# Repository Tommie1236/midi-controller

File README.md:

<!---->

### huge thanks to the amazing [rp2040 skeleton project](https://github.com/daveythacher/RP2040_SKELETON). it helped immensly setting up this project. i probably couldn't have done it without

# &lt;still need good name :)&gt;
#### A lighting focused midi controller

---
### Why?
I started this project as i wanted phisical controls to go with the [mydmx3](https://www.adj.com/mydmx-3) dmx controller software.  
Mydmx3 practicly only support midi as data in/out next to dmx out. So a midi controller it is.  
There are more than enough midi controllers on the market but almost all of them are audio focused in the controls. I couldn't really vind any that i would like for controlling lighting. So i decided to design and build my own.

### Requirements
I set a couple of requirements that i definetly wanted in my controler. As following:  
#### Controls:

- **motorized faders**. Mostly for dimming controls, enough in the playback section and 1 as Master.  
  I chose motorized so they could sync with the controlling software if the value changes and for for example if you were to switch banks to a new set of controls. (mydmx doesn't support that but i wanted to design my controller to work with almost anything.)

- **Buttons**. for playbacks/executors en general control, a whole lot.  
  Of Course. what would a controller be without a lot of buttons. I also want them to have black with transparent text keycaps and rgb leds below to show the status of the button.

- **Encoders**. Mostly speed control but could also be dimmer, at least 1 per "channel"/collumn and a couple spare.
  I wanted some encoders to be able to change the speed of scene/cue playbacks. But also for for example a dimmer channel dat isn't changed often but often enough to have phisical controls for.

- **Small Displays/Scribble Strips**. channel/collumn names, one per channel/collumn.  
  To show what cue/scene was mapped to that channel/collumn. If i implement bank switching inside the controller (as mydmx doesn't support like anything. only the most basic midi triggering) i want to see what cue i have mapped on that fader/buttons.
  And maybe also to show the fader/encoder value when changing. For if you want it to a specific value and the visual position isn't enough.

- **Keypad**. just one, numbers 0-9 + some modifiers.  
  Should speak for itself. just general number inputs and modifiers.

- **"Master" Display**. (relatively) big display, just one.  
   A around 3a4" touch display for configuration of the controller and general info. Main controls for anything happening inside the controller.

- **Leds**. A lot. most RGB some just Amber.  
  I want all the buttons to have a seperate controllable RGB led to show the buttons status. and about 16 mono Amber leds around the encoders to show their value.

#### Conectivity:

- **usb midi**. one usb-B port.
  To connect to a pc running for example mydmx.

- **hardware midi**. 2 or 3 din-5 ports.
  To connect to other midi gear or any controller that has hardware midi ports on it. Should have the same data as the usb midi port

- **External Switch Ports**. 2a3 x 1/4" jack.
  To connect external footswitches or pedals. should support normal on/off footswitches and maybe one or 2 can have analog value support.

- **Desk Light**. xlr-4?.
  A xlr connector that support a lot of desk lights. preferably xlr-4 so it isn't confused with audio or dmx signals. Sadly there isn't a standard for desk ligths as far as i can find.

- **Powercon Socket**. Blue one. maybe also power out.  
  Of cource. It needs some power to run. prefereably powercon (true1??) but a C14 socket would also work.  
  with the motor faders and a lot of leds. Usb supplied power wont be enough.

#### And here are some features i want to support but arent required for the mvp: 

- **USB Hub**. Probably USB-A sockets.  
  To connect more devices downstream from the controller

- **RTP MIDI**. Wifi/Ethernet  
  Using a ESP32 or similar to handle the network stack and enable the controller to communicate either wireless or via a ethernet cable.  
  Adding to the already available midi connection options of USB-MIDI and hardware-MIDI

- **Web Server**.  
  Maybe a configuration webserver as the display will be quite small. would also run on the ESP32 that handels the network.  
  it connects to the main rp2040 using uart.

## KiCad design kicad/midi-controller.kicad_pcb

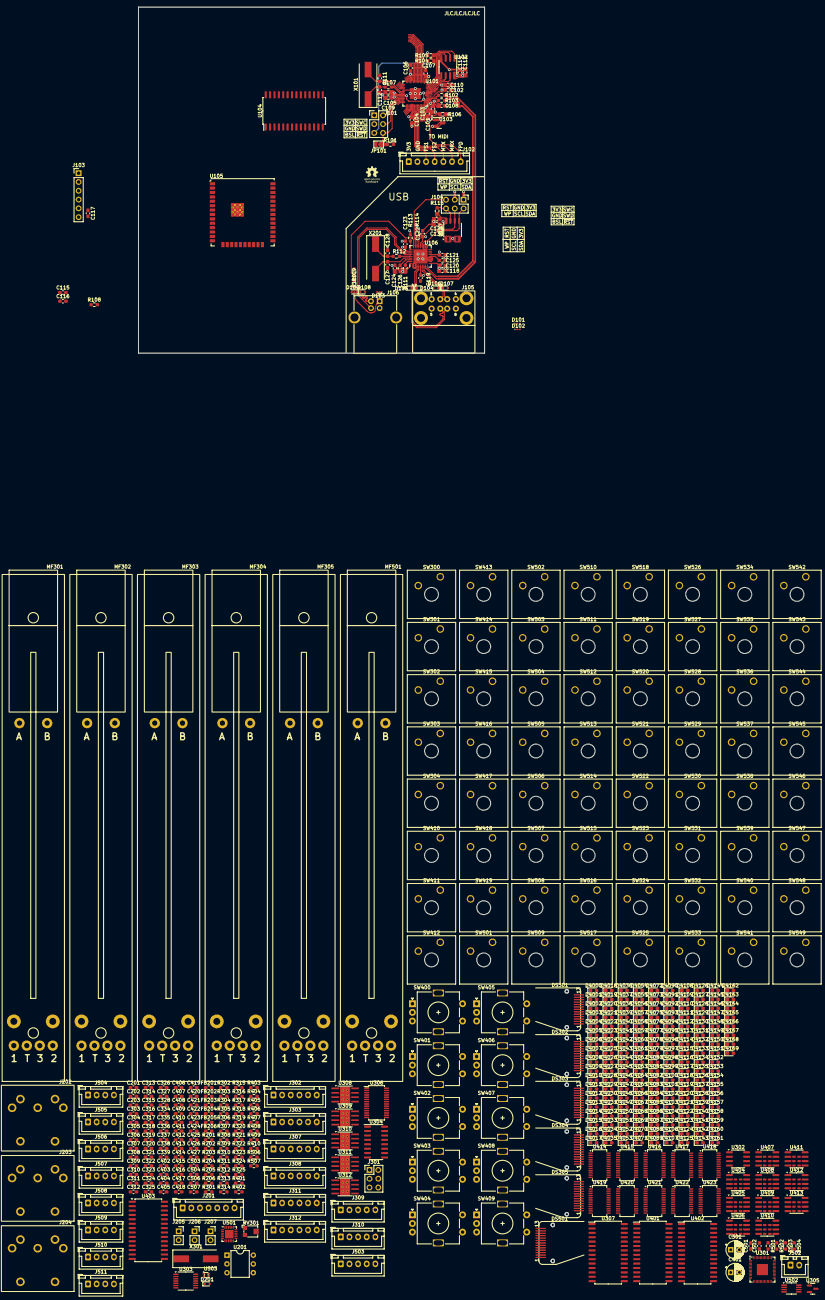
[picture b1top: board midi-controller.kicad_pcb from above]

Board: 4 copper layers, 516 parts (0 on the bottom side), 480 nets.

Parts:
C101, C108, C115, C117, C118, C129, C305, C312, C313, C315, C317, C321, C323, C325, C327, C334, C402, C404, C406, C408, C410, C412, C414, C416, C418, C420, C422, C424, C426, C501, C503: 1u; C_0603_1608Metric_Pad1.08x0.95mm_HandSolder
C102, C103, C104, C105, C106, C107, C109, C110, C114, C116, C119, C120, C121, C122, C123, C124, C125, C126, C130, C303, C304, C306, C307, C308, C309, C310, C311, C314, C316, C318, C320, C322, C324, C326, C328, C335, C337, C403, C405, C407, C409, C411, C413, C415, C417, C419, C421, C423, C425, C427, C502, C504, C507: 100n; C_0603_1608Metric_Pad1.08x0.95mm_HandSolder
C111, C112, C127, C128, C338, C339: 27p; C_0603_1608Metric_Pad1.08x0.95mm_HandSolder
C113, C336: 2u2; C_0603_1608Metric_Pad1.08x0.95mm_HandSolder
C201, C202, C203: 100nf; C_0603_1608Metric_Pad1.08x0.95mm_HandSolder
C301, C401: 10uf; CP_Radial_D5.0mm_P2.50mm
C319, C506: 100u; C_0603_1608Metric_Pad1.08x0.95mm_HandSolder
D101, D102, D103: 5v5; D_0201_0603Metric_Pad0.64x0.40mm_HandSolder
D104, D105, D106, D107, D108, D109: 3v6; D_SOD-523
D201: 1N914; D_SOD-523
D4000, D4001, D4002, D4003, D4004, D4005, D4006, D4007, D4008, D4009, D4010, D4011, D4012, D4013, D4014, D4015, D4016, D4017, D4018, D4019, D4020, D4021, D4022, D4023, D4024, D4025, D4026, D4027, D4028, D4029, D4030, D4031, D4032, D4033, D4034, D4035, D4036, D4037, D4038, D4039, D4040, D4041, D4042, D4043, D4044, D4045, D4046, D4047, D4048, D4049, D4050, D4051, D4052, D4053, D4054, D4055, D4056, D4057, D4058, D4059, D4060, D4061, D4062, D4063, D4064, D4065, D4066, D4067, D4068, D4069, D4070, D4071, D4072, D4073, D4074, D4075, D4076, D4077, D4078, D4079, D4080, D4081, D4082, D4083, D4084, D4085, D4086, D4087, D4088, D4089, D4090, D4091, D4092, D4093, D4094, D4095, D4096, D4097, D4098, D4099, D4100, D4101, D4102, D4103, D4104, D4105, D4106, D4107, D4108, D4109, D4110, D4111, D4112, D4113, D4114, D4115, D4116, D4117, D4118, D4119, D4120, D4121, D4122, D4123, D4124, D4125, D4126, D4127, D4128, D4129, D4130, D4131, D4132, D4133, D4134, D4135, D4136, D4137, D4138, D4139, D4140, D4141, D4142, D4143, D4144, D4145, D4146, D4147, D4148, D4149, D4150, D4151, D4152, D4153, D4154, D4155, D4156, D4157, D4158, D4159, D4160, D4161, D4162, D4163, D4164, D4165, D4166, D4167, D4168, D4169: LED; LED_0603_1608Metric_Pad1.05x0.95mm_HandSolder
DS301, DS302, DS303, DS304, DS305: 1.05'_120x240_spi_screen; 1.05' 120x240 spi screen
DS501: 1.05" 130*240 spi screen; 1.05' 120z240 spi screen
FB201, FB202, FB203, FB204, FB205, FB206: 1K@100MHz; L_0603_1608Metric_Pad1.05x0.95mm_HandSolder
J101, J104, J301: Conn_02x03_Counter_Clockwise; PinHeader_2x03_P2.54mm_Vertical
J102, J201: Conn_01x07_Socket; JST_XH_B7B-XH-A_1x07_P2.50mm_Vertical
J103: Conn_01x06_Socket; PinHeader_1x06_P2.54mm_Vertical
J105: USB_A_Stacked; USB1035_USB-A2_STACKED
J106: USB_B; USB_B_OST_USB-B1HSxx_Horizontal
J202, J203, J204: DIN-5_180degree; DIN5-180
J205, J206: AudioJack2; PinSocket_1x02_P2.54mm_Vertical
J207: AudioJack3; PinSocket_1x02_P2.54mm_Vertical
J302, J303, J307, J308, J311, J312: Conn_01x06_Socket; JST_XH_B6B-XH-A_1x06_P2.50mm_Vertical
J309, J310, J503: Conn_01x05_Socket; JST_XH_B5B-XH-A_1x05_P2.50mm_Vertical
J502: Conn_01x02_Socket; JST_XH_B2B-XH-A_1x02_P2.50mm_Vertical
J504, J505, J506, J507, J508, J509, J510, J511: Conn_01x04_Socket; JST_XH_B4B-XH-A_1x04_P2.50mm_Vertical
JP101: SolderJumper_2_Open; SolderJumper-2_P1.3mm_Open_TrianglePad1.0x1.5mm
MF301, MF302, MF303, MF304, MF305, MF501: RSA0N11M9A0J
R101, R304, R310, R311, R312, R313, R314, R506, R507: 10K; R_0603_1608Metric_Pad0.98x0.95mm_HandSolder
R102, R103: 27; R_0603_1608Metric_Pad0.98x0.95mm_HandSolder
R104, R107, R112, R301, R303: 1K; R_0603_1608Metric_Pad0.98x0.95mm_HandSolder
R105, R302: NFIT; R_0603_1608Metric_Pad0.98x0.95mm_HandSolder
R106, R315: R; R_0603_1608Metric_Pad0.98x0.95mm_HandSolder
R108: 10k; R_0603_1608Metric_Pad0.98x0.95mm_HandSolder
R109, R110, R113, R114, R115: 100K; R_0603_1608Metric_Pad0.98x0.95mm_HandSolder
R111: 12K; R_0603_1608Metric_Pad0.98x0.95mm_HandSolder
R201: 470; R_0603_1608Metric_Pad0.98x0.95mm_HandSolder
R202, R204: 33; R_0603_1608Metric_Pad0.98x0.95mm_HandSolder
R203, R205, R316, R317, R318, R319, R320: 10; R_0603_1608Metric_Pad0.98x0.95mm_HandSolder
R206: 220; R_0603_1608Metric_Pad0.98x0.95mm_HandSolder
R305, R306, R307, R308, R309, R501, R502, R503, R504: 4K7; R_0603_1608Metric_Pad0.98x0.95mm_HandSolder
R321, R322, R323, R324, R325: 80K; R_0603_1608Metric_Pad0.98x0.95mm_HandSolder
R401, R402, R403, R404, R405, R406, R407, R408, R409, R410: 2K5; R_0603_1608Metric_Pad0.98x0.95mm_HandSolder
RV301: R_Potentiometer; Potentiometer_Bourns_TC33X_Vertical
SW300, SW301, SW302, SW303, SW304, SW410, SW411, SW412, SW413, SW414, SW415, SW416, SW417, SW418, SW419, SW501, SW502, SW503, SW504, SW505, SW506, SW507, SW508, SW509, SW510, SW511, SW512, SW513, SW514, SW515, SW516, SW517, SW518, SW519, SW521, SW522, SW523, SW524, SW525, SW526, SW527, SW528, SW529, SW530, SW531, SW532, SW533, SW534, SW535, SW536, SW537, SW538, SW539, SW540, SW541, SW542, SW543, SW544, SW545, SW546, SW547, SW548, SW549: SW_SPST; SW_Cherry_MX_1.00u_Plate
SW400, SW401, SW402, SW403, SW404, SW405, SW406, SW407, SW408, SW409: RotaryEncoder_Switch; RotaryEncoder_Alps_EC11E-Switch_Vertical_H20mm
SW520: SW_SPST; SW_Cherry_MX_2.00u_Vertical_Plate
U101, U301: RP2040; QFN-56-1EP_7x7mm_P0.4mm_EP3.2x3.2mm
U102, U302: AT25SF081-SSHD-X; SOIC-8_3.9x4.9mm_P1.27mm
U103, U305: LM4040D33; SOT-23
U104, U307, U401, U402, U403: MCP23S17_SO; SOIC-28W_7.5x17.9mm_P1.27mm
U105: ESP32-WROOM-32U
U106: USB2514B_Bi; QFN-36-1EP_6x6mm_P0.5mm_EP4.1x4.1mm
U107: 24LC02; SOP-8_3.9x4.9mm_P1.27mm
U201: H11L1; DIP-6_W7.62mm
U303: MTCH105; TSSOP-14_4.4x5mm_P0.65mm
U304: MCP3008; SOIC-16_3.9x9.9mm_P1.27mm
U306: PCA9635; TSSOP-28_4.4x9.7mm_P0.65mm
U308, U309, U310, U311, U312: DRV8871DDA; Texas_HTSOP-8-1EP_3.9x4.9mm_P1.27mm_EP2.95x4.9mm_Mask2.4x3.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
U404, U405, U406, U407, U408, U409, U410, U411, U412, U413: LS30; SOIC-8_3.9x4.9mm_P1.27mm
U414, U415, U416, U417, U418, U419, U420, U421, U422, U423: TLC59282; SSOP-24_3.9x8.7mm_P0.635mm
U501: TCA8418; WQFN-24-1EP_4x4mm_P0.5mm_EP2.45x2.45mm
U502: MTCH102; MSOP-8_3x3mm_P0.65mm
U503: DRV8210; SOT-6
X101, X301: 12Mhz; Crystal_SMD_HC49-SD
X201: 24Mhz; Crystal_SMD_HC49-SD

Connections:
+1V1: C108.1, C109.1, C110.1, C303.1, C304.1, C312.1, U101.23 (DVDD), U101.45 (VREG_VOUT), U101.50 (DVDD), U301.23 (DVDD), U301.45 (VREG_VOUT), U301.50 (DVDD)
+3V3: C101.1, C102.1, C103.1, C104.1, C105.1, C106.1, C107.1, C113.1, C114.1, C115.1, C116.1, C117.1, C118.1, C119.1, C120.1, C121.1, C122.1, C123.1, C124.1, C129.1, C130.1, C201.1, C501.1, C502.1, C503.1, C504.1, DS501.10 (VCC), J101.1, J102.1, J103.5, J104.1, J201.1, J503.2, R101.1, R105.1, R106.1, R108.1, R113.1, R114.1, R115.1, R201.2, R202.2, R204.2, R501.1, R502.1, R503.1, R504.1, R506.1, R507.1, U101.1 (IOVDD), U101.10 (IOVDD), U101.22 (IOVDD), U101.33 (IOVDD), U101.42 (IOVDD), U101.44 (VREG_IN), U101.48 (USB_VDD), U101.49 (IOVDD), U102.8 (VCC), U104.9 (VDD), U106.5 (VDDA33), U106.10 (VDDA33), U106.15 (VDD33), U106.23 (VDD33), U106.29 (VDDA33), U106.36 (VDDA33), U107.8 (VCC), U201.6, U501.21 (VCC), U502.1 (VCC), U502.4 (LPMS)
+E3V3: C401.1, C402.1, C403.1, C404.1, C405.1, C406.1, C407.1, C408.1, C409.1, C410.1, C411.1, C412.1, C413.1, C414.1, C415.1, C416.1, C417.1, C420.1, C421.1, C422.1, C423.1, C424.1, C425.1, C426.1, C427.1, D4000.2 (A), D4001.2 (A), D4002.2 (A), D4003.2 (A), D4004.2 (A), D4005.2 (A), D4006.2 (A), D4007.2 (A), D4008.2 (A), D4009.2 (A), D4010.2 (A), D4011.2 (A), D4012.2 (A), D4013.2 (A), D4014.2 (A), D4015.2 (A), D4016.2 (A), D4017.2 (A), D4018.2 (A), D4019.2 (A), D4020.2 (A), D4021.2 (A), D4022.2 (A), D4023.2 (A), D4024.2 (A), D4025.2 (A), D4026.2 (A), D4027.2 (A), D4028.2 (A), D4029.2 (A), D4030.2 (A), D4031.2 (A), D4032.2 (A), D4033.2 (A), D4034.2 (A), D4035.2 (A), D4036.2 (A), D4037.2 (A), D4038.2 (A), D4039.2 (A), D4040.2 (A), D4041.2 (A), D4042.2 (A), D4043.2 (A), D4044.2 (A), D4045.2 (A), D4046.2 (A), D4047.2 (A), D4048.2 (A), D4049.2 (A), D4050.2 (A), D4051.2 (A), D4052.2 (A), D4053.2 (A), D4054.2 (A), D4055.2 (A), D4056.2 (A), D4057.2 (A), D4058.2 (A), D4059.2 (A), D4060.2 (A), D4061.2 (A), D4062.2 (A), D4063.2 (A), D4064.2 (A), D4065.2 (A), D4066.2 (A), D4067.2 (A), D4068.2 (A), D4069.2 (A), D4070.2 (A), D4071.2 (A), D4072.2 (A), D4073.2 (A), D4074.2 (A), D4075.2 (A), D4076.2 (A), D4077.2 (A), D4078.2 (A), D4079.2 (A), D4080.2 (A), D4081.2 (A), D4082.2 (A), D4083.2 (A), D4084.2 (A), D4085.2 (A), D4086.2 (A), D4087.2 (A), D4088.2 (A), D4089.2 (A), D4090.2 (A), D4091.2 (A), D4092.2 (A), D4093.2 (A), D4094.2 (A), D4095.2 (A), D4112.2 (A), D4113.2 (A), D4114.2 (A), D4115.2 (A), D4116.2 (A), D4117.2 (A), D4118.2 (A), D4119.2 (A), D4120.2 (A), D4121.2 (A), D4122.2 (A), D4123.2 (A), D4124.2 (A), D4125.2 (A), D4126.2 (A), D4127.2 (A), D4128.2 (A), D4129.2 (A), D4130.2 (A), D4131.2 (A), D4132.2 (A), D4133.2 (A), D4134.2 (A), D4135.2 (A), D4136.2 (A), D4137.2 (A), D4138.2 (A), D4139.2 (A), D4140.2 (A), D4141.2 (A), D4142.2 (A), D4143.2 (A), D4144.2 (A), D4145.2 (A), D4146.2 (A), D4147.2 (A), D4148.2 (A), D4149.2 (A), D4150.2 (A), D4151.2 (A), D4152.2 (A), D4153.2 (A), D4154.2 (A), D4155.2 (A), D4156.2 (A), D4157.2 (A), D4158.2 (A), D4159.2 (A), D4160.2 (A), D4161.2 (A), D4162.2 (A), D4163.2 (A), D4164.2 (A), D4165.2 (A), D4167.2 (A), D4168.2 (A), D4169.2 (A), DS301.10 (VCC), DS302.10 (VCC), DS303.10 (VCC), DS304.10 (VCC), DS305.10 (VCC), J310.2, R316.2, R317.2, R318.2, R319.2, R320.2, U401.9 (VDD), U402.9 (VDD), U403.9 (VDD), U404.1 (VCC), U405.1 (VCC), U406.1 (VCC), U407.1 (VCC), U408.1 (VCC), U409.1 (VCC), U410.1 (VCC), U411.1 (VCC), U412.1 (VCC), U413.1 (VCC), U414.24 (VCC), U415.24 (VCC), U416.24 (VCC), U417.24 (VCC), U418.24 (VCC), U420.24 (VCC), U421.24 (VCC), U422.24 (VCC), U423.24 (VCC)
+F3V3: C301.1, C305.1, C306.1, C307.1, C308.1, C309.1, C310.1, C311.1, C313.1, C314.1, C315.1, C316.1, C317.1, C318.1, C334.1, C335.1, C336.1, C337.1, J301.1, J309.4, MF301.1, MF302.1, MF303.1, MF304.1, MF305.1, R302.1, R304.1, R310.2, R311.2, R312.2, R313.2, R314.2, R315.1, U301.1 (IOVDD), U301.10 (IOVDD), U301.22 (IOVDD), U301.33 (IOVDD), U301.42 (IOVDD), U301.44 (VREG_IN), U301.48 (USB_VDD), U301.49 (IOVDD), U302.8 (VCC), U303.1 (VCC), U303.4 (LPMS), U304.16 (Vdd), U306.28 (VDD), U307.9 (VDD)
/Fader-bank/FXIN: C338.2, U301.20 (XIN), X301.2
/Fader-bank/FXOUT: R301.2, U301.21 (XOUT)
/Fader-bank/F_QSPI_CS: R302.2, R303.1, U301.56 (QSPI_SCS), U302.1 (~CS)
/Fader-bank/F_QSPI_SCL: U301.52 (QSPI_SCLK), U302.6 (SCK)
/Fader-bank/F_QSPI_SD0: U301.53 (QSPI_SD0), U302.5 (SI/IO0)
/Fader-bank/F_QSPI_SD1: U301.55 (QSPI_SD1), U302.2 (SO/IO1)
/Fader-bank/F_QSPI_SD2: U301.54 (QSPI_SD2), U302.3 (~WP/IO2)
/Fader-bank/F_QSPI_SD3: U301.51 (QSPI_SD3), U302.7 (~HOLD/IO3)
/QSPI_CS: R104.1, R105.2, U101.56 (QSPI_SCS), U102.1 (~CS)
/QSPI_SCL: U101.52 (QSPI_SCLK), U102.6 (SCK)
/QSPI_SD0: U101.53 (QSPI_SD0), U102.5 (SI/IO0)
/QSPI_SD1: U101.55 (QSPI_SD1), U102.2 (SO/IO1)
/QSPI_SD2: U101.54 (QSPI_SD2), U102.3 (~WP/IO2)
/QSPI_SD3: U101.51 (QSPI_SD3), U102.7 (~HOLD/IO3)
/SPI0_01_R: R108.2, U104.18 (~RESET)
/USB/CRFILT: C125.1, U106.14 (CRFILT)
/USB/HS_IND: R114.2, U106.25 (HS_IND/CFG_SEL1)
/USB/PLLFILT: C126.1, U106.34 (PLLFILT)
/USB/RBIAS: R111.2, U106.35 (RBIAS)
/USB/SUSP_IND: R113.2, U106.28 (SUSP_IND/LOCAL_PWR/NON_REM0)
/USB/VBUS_DET: R109.2, R110.1, U106.27 (VBUS_DET)
/USB/XTALIN: C127.2, U106.33 (XTALIN/CLKIN), X201.2
/USB/XTALOUT: R112.2, U106.32 (XTALOUT)
/USB_RP2_DN: R103.2, U101.46 (USB_DN)
/USB_RP2_DP: R102.2, U101.47 (USB_DP)
B00: J303.5, SW300.2 (B)
B00F: J302.2, U307.4 (GPB3)
B01: J303.4, SW301.2 (B)
B01F: J302.3, U307.5 (GPB4)
B02: J303.3, SW302.2 (B)
B02F: J302.4, U307.6 (GPB5)
B03: J303.2, SW303.2 (B)
B03F: J302.5, U307.7 (GPB6)
B04: J303.1, SW304.2 (B)
B04F: J302.6, U307.8 (GPB7)
B05: SW410.2 (B), U401.25 (GPA4)
B06: SW411.1 (A), U401.4 (GPB3)
B07: SW412.2 (B), U402.25 (GPA4)
B08: SW413.1 (A), U402.4 (GPB3)
B09: SW414.1 (A), U403.4 (GPB3)
B10: SW415.2 (B), U401.24 (GPA3)
B11: SW416.1 (A), U401.5 (GPB4)
B12: SW417.2 (B), U402.24 (GPA3)
B13: SW418.1 (A), U402.5 (GPB4)
B14: SW419.1 (A), U403.5 (GPB4)
BGND: J303.6, SW300.1 (A), SW301.1 (A), SW302.1 (A), SW303.1 (A), SW304.1 (A)
BOOTSEL: J101.3, R104.2
COL0: SW501.2 (B), SW505.2 (B), SW509.2 (B), SW513.2 (B), SW517.2 (B), SW521.2 (B), U501.9 (COL0)
COL1: SW502.2 (B), SW506.2 (B), SW510.2 (B), SW514.2 (B), SW518.2 (B), SW522.2 (B), U501.10 (COL1)
COL2: SW503.2 (B), SW507.2 (B), SW511.2 (B), SW515.2 (B), SW519.2 (B), SW523.2 (B), U501.11 (COL2)
COL3: SW504.2 (B), SW508.2 (B), SW512.2 (B), SW516.2 (B), SW520.2 (B), U501.12 (COL3)
COL4: J504.2, J508.2, SW524.2 (B), SW525.2 (B), U501.13 (COL4)
COL5: J504.1, J508.1, U501.14 (COL5)
COL6: J506.4, J510.4, U501.15 (COL6)
COL7: J506.3, J510.3, U501.16 (COL7)
COL8: J506.2, J510.2, U501.17 (COL8)
COL9: J506.1, J510.1, U501.18 (COL9)
CS_U6: U101.16 (GPIO13), U104.11 (~CS)
CS_U11: J307.2, U301.6 (GPIO4)
CS_U11-ENC: J308.2, U401.11 (~CS)
CS_U12: J307.4, U301.4 (GPIO2)
CS_U12-ENC: J308.4, U402.11 (~CS)
CS_U13: J307.6, U301.2 (GPIO0)
CS_U13-ENC: J308.6, U403.11 (~CS)
CS_U14: U301.13 (GPIO10), U307.11 (~CS)
DS0CS: DS301.7 (CS), DS501.7 (CS), U403.24 (GPA3)
DS1CS: DS302.7 (CS), U403.25 (GPA4)
DS2CS: DS303.7 (CS), U403.26 (GPA5)
DS3CS: DS304.7 (CS), U403.27 (GPA6)
DS4CS: DS305.7 (CS), U403.28 (GPA7)
E1A: SW401.A, U405.2 (A)
E1B: SW401.B, U405.3 (B)
E1S: SW401.S1, U405.4 (SWI)
E2A: SW402.A, U406.2 (A)
E2B: SW402.B, U406.3 (B)
E2S: SW402.S1, U406.4 (SWI)
E3A: SW403.A, U407.2 (A)
E3B: SW403.B, U407.3 (B)
E3S: SW403.S1, U407.4 (SWI)
E4A: SW404.A, U408.2 (A)
E4B: SW404.B, U408.3 (B)
E4S: SW404.S1, U408.4 (SWI)
E5A: SW405.A, U409.2 (A)
E5B: SW405.B, U409.3 (B)
E5S: SW405.S2, U409.4 (SWI)
E6A: SW406.A, U410.2 (A)
E6B: SW406.B, U410.3 (B)
E6S: SW406.S2, U410.4 (SWI)
E7A: SW407.A, U411.2 (A)
E7B: SW407.B, U411.3 (B)
E7S: SW407.S2, U411.4 (SWI)
E8A: SW408.A, U412.2 (A)
E8B: SW408.B, U412.3 (B)
E8S: SW408.S2, U412.4 (SWI)
E9A: SW409.A, U413.2 (A)
E9B: SW409.B, U413.3 (B)
E9S: SW409.S2, U413.4 (SWI)
EEP_WP: J104.4, R115.2, U107.7 (WP)
EGND: C401.2, C402.2, C403.2, C404.2, C405.2, C406.2, C407.2, C408.2, C409.2, C410.2, C411.2, C412.2, C413.2, C414.2, C415.2, C416.2, C417.2, C418.2, C419.2, C420.2, C421.2, C422.2, C423.2, C424.2, C425.2, DS301.8 (GND), DS301.13 (GND), DS302.8 (GND), DS302.13 (GND), DS303.8 (GND), DS303.13 (GND), DS304.8 (GND), DS304.13 (GND), DS305.8 (GND), DS305.13 (GND), J310.1, R401.1, R402.1, R403.1, R404.1, R405.1, R406.1, R407.1, R408.1, R409.1, R410.1, SW400.C, SW400.S2, SW401.C, SW401.S2, SW402.C, SW402.S2, SW403.C, SW403.S2, SW404.C, SW404.S2, SW405.C, SW405.S1, SW406.C, SW406.S1, SW407.C, SW407.S1, SW408.C, SW408.S1, SW409.C, SW409.S1, SW410.1 (A), SW411.2 (B), SW412.1 (A), SW413.2 (B), SW414.2 (B), SW415.1 (A), SW416.2 (B), SW417.1 (A), SW418.2 (B), SW419.2 (B), U401.10 (VSS), U401.15 (A0), U401.16 (A1), U401.17 (A2), U402.10 (VSS), U402.15 (A0), U402.16 (A1), U402.17 (A2), U403.10 (VSS), U403.15 (A0), U403.16 (A1), U403.17 (A2), U404.8 (GND), U405.8 (GND), U406.8 (GND), U407.8 (GND), U408.8 (GND), U409.8 (GND), U410.8 (GND), U411.8 (GND), U412.8 (GND), U413.8 (GND), U414.1 (GND), U415.1 (GND), U416.1 (GND), U417.1 (GND), U418.1 (GND), U419.1 (GND), U421.1 (GND), U422.1 (GND), U423.1 (GND)
ENC0-0: D4000.1 (K), U414.5 (OUT0)
ENC0-1: D4001.1 (K), U414.6 (OUT1)
ENC0-2: D4002.1 (K), U414.7 (OUT2)
ENC0-3: D4003.1 (K), U414.8 (OUT3)
ENC0-4: D4004.1 (K), U414.9 (OUT4)
ENC0-5: D4005.1 (K), U414.10 (OUT5)
ENC0-6: D4006.1 (K), U414.11 (OUT6)
ENC0-7: D4007.1 (K), U414.12 (OUT7)
ENC0-8: D4008.1 (K), U414.20 (OUT15)
ENC0-9: D4009.1 (K), U414.19 (OUT14)
ENC0-10: D4010.1 (K), U414.18 (OUT13)
ENC0-11: D4011.1 (K), U414.17 (OUT12)
ENC0-12: D4012.1 (K), U414.16 (OUT11)
ENC0-13: D4013.1 (K), U414.15 (OUT10)
ENC0-14: D4014.1 (K), U414.14 (OUT9)
ENC0-15: D4015.1 (K), U414.13 (OUT8)
ENC1-0: D4016.1 (K), U415.5 (OUT0)
ENC1-1: D4017.1 (K), U415.6 (OUT1)
ENC1-2: D4018.1 (K), U415.7 (OUT2)
ENC1-3: D4019.1 (K), U415.8 (OUT3)
ENC1-4: D4020.1 (K), U415.9 (OUT4)
ENC1-5: D4021.1 (K), U415.10 (OUT5)
ENC1-6: D4022.1 (K), U415.11 (OUT6)
ENC1-7: D4023.1 (K), U415.12 (OUT7)
ENC1-8: D4024.1 (K), U415.20 (OUT15)
ENC1-9: D4025.1 (K), U415.19 (OUT14)
ENC1-10: D4026.1 (K), U415.18 (OUT13)
ENC1-11: D4027.1 (K), U415.17 (OUT12)
ENC1-12: D4028.1 (K), U415.16 (OUT11)
ENC1-13: D4029.1 (K), U415.15 (OUT10)
ENC1-14: D4030.1 (K), U415.14 (OUT9)
ENC1-15: D4031.1 (K), U415.13 (OUT8)
ENC2-0: D4032.1 (K), U416.5 (OUT0)
ENC2-1: D4033.1 (K), U416.6 (OUT1)
ENC2-2: D4034.1 (K), U416.7 (OUT2)
ENC2-3: D4035.1 (K), U416.8 (OUT3)
ENC2-4: D4036.1 (K), U416.9 (OUT4)
ENC2-5: D4037.1 (K), U416.10 (OUT5)
ENC2-6: D4038.1 (K), U416.11 (OUT6)
ENC2-7: D4039.1 (K), U416.12 (OUT7)
ENC2-8: D4040.1 (K), U416.20 (OUT15)
ENC2-9: D4041.1 (K), U416.19 (OUT14)
ENC2-10: D4042.1 (K), U416.18 (OUT13)
ENC2-11: D4043.1 (K), U416.17 (OUT12)
ENC2-12: D4044.1 (K), U416.16 (OUT11)
ENC2-13: D4045.1 (K), U416.15 (OUT10)
ENC2-14: D4046.1 (K), U416.14 (OUT9)
ENC2-15: D4047.1 (K), U416.13 (OUT8)
ENC3-0: D4048.1 (K), U417.5 (OUT0)
ENC3-1: D4049.1 (K), U417.6 (OUT1)
ENC3-2: D4050.1 (K), U417.7 (OUT2)
ENC3-3: D4051.1 (K), U417.8 (OUT3)
ENC3-4: D4052.1 (K), U417.9 (OUT4)
ENC3-5: D4053.1 (K), U417.10 (OUT5)
ENC3-6: D4054.1 (K), U417.11 (OUT6)
ENC3-7: D4055.1 (K), U417.12 (OUT7)
ENC3-8: D4056.1 (K), U417.20 (OUT15)
ENC3-9: D4057.1 (K), U417.19 (OUT14)
ENC3-10: D4058.1 (K), U417.18 (OUT13)
ENC3-11: D4059.1 (K), U417.17 (OUT12)
ENC3-12: D4060.1 (K), U417.16 (OUT11)
ENC3-13: D4061.1 (K), U417.15 (OUT10)
ENC3-14: D4062.1 (K), U417.14 (OUT9)
ENC3-15: D4063.1 (K), U417.13 (OUT8)
ENC4-0: D4064.1 (K), U418.5 (OUT0)
ENC4-1: D4065.1 (K), U418.6 (OUT1)
ENC4-2: D4066.1 (K), U418.7 (OUT2)
ENC4-3: D4067.1 (K), U418.8 (OUT3)
ENC4-4: D4068.1 (K), U418.9 (OUT4)
ENC4-5: D4069.1 (K), U418.10 (OUT5)
ENC4-6: D4070.1 (K), U418.11 (OUT6)
ENC4-7: D4071.1 (K), U418.12 (OUT7)
ENC4-8: D4072.1 (K), U418.20 (OUT15)
ENC4-9: D4073.1 (K), U418.19 (OUT14)
ENC4-10: D4074.1 (K), U418.18 (OUT13)
ENC4-11: D4075.1 (K), U418.17 (OUT12)
ENC4-12: D4076.1 (K), U418.16 (OUT11)
ENC4-13: D4077.1 (K), U418.15 (OUT10)
ENC4-14: D4078.1 (K), U418.14 (OUT9)
ENC4-15: D4079.1 (K), U418.13 (OUT8)
ENC5-0: D4080.1 (K), U419.5 (OUT0)
ENC5-1: D4081.1 (K), U419.6 (OUT1)
ENC5-2: D4082.1 (K), U419.7 (OUT2)
ENC5-3: D4083.1 (K), U419.8 (OUT3)
ENC5-4: D4084.1 (K), U419.9 (OUT4)
ENC5-5: D4085.1 (K), U419.10 (OUT5)
ENC5-6: D4086.1 (K), U419.11 (OUT6)
ENC5-7: D4087.1 (K), U419.12 (OUT7)
ENC5-8: D4088.1 (K), U419.20 (OUT15)
ENC5-9: D4089.1 (K), U419.19 (OUT14)
ENC5-10: D4090.1 (K), U419.18 (OUT13)
ENC5-11: D4091.1 (K), U419.17 (OUT12)
ENC5-12: D4092.1 (K), U419.16 (OUT11)
ENC5-13: D4093.1 (K), U419.15 (OUT10)
ENC5-14: D4094.1 (K), U419.14 (OUT9)
ENC5-15: D4095.1 (K), U419.13 (OUT8)
ENC6-0: D4096.1 (K), U420.5 (OUT0)
ENC6-1: D4097.1 (K), U420.6 (OUT1)
ENC6-2: D4098.1 (K), U420.7 (OUT2)
ENC6-3: D4099.1 (K), U420.8 (OUT3)
ENC6-4: D4100.1 (K), U420.9 (OUT4)
ENC6-5: D4101.1 (K), U420.10 (OUT5)
ENC6-6: D4102.1 (K), U420.11 (OUT6)
ENC6-7: D4103.1 (K), U420.12 (OUT7)
ENC6-8: D4104.1 (K), U420.20 (OUT15)
ENC6-9: D4105.1 (K), U420.19 (OUT14)
ENC6-10: D4106.1 (K), U420.18 (OUT13)
ENC6-11: D4107.1 (K), U420.17 (OUT12)
ENC6-12: D4108.1 (K), U420.16 (OUT11)
ENC6-13: D4109.1 (K), U420.15 (OUT10)
ENC6-14: D4110.1 (K), U420.14 (OUT9)
ENC6-15: D4111.1 (K), U420.13 (OUT8)
ENC7-0: D4112.1 (K), U421.5 (OUT0)
ENC7-1: D4113.1 (K), U421.6 (OUT1)
ENC7-2: D4114.1 (K), U421.7 (OUT2)
ENC7-3: D4115.1 (K), U421.8 (OUT3)
ENC7-4: D4116.1 (K), U421.9 (OUT4)
ENC7-5: D4117.1 (K), U421.10 (OUT5)
ENC7-6: D4118.1 (K), U421.11 (OUT6)
ENC7-7: D4119.1 (K), U421.12 (OUT7)
ENC7-8: D4120.1 (K), U421.20 (OUT15)
ENC7-9: D4121.1 (K), U421.19 (OUT14)
ENC7-10: D4122.1 (K), U421.18 (OUT13)
ENC7-11: D4123.1 (K), U421.17 (OUT12)
ENC7-12: D4124.1 (K), U421.16 (OUT11)
ENC7-13: D4125.1 (K), U421.15 (OUT10)
ENC7-14: D4126.1 (K), U421.14 (OUT9)
ENC7-15: D4127.1 (K), U421.13 (OUT8)
ENC8-0: D4128.1 (K), U422.5 (OUT0)
ENC8-1: D4129.1 (K), U422.6 (OUT1)
ENC8-2: D4130.1 (K), U422.7 (OUT2)
ENC8-3: D4131.1 (K), U422.8 (OUT3)
ENC8-4: D4132.1 (K), U422.9 (OUT4)
ENC8-5: D4133.1 (K), U422.10 (OUT5)
ENC8-6: D4134.1 (K), U422.11 (OUT6)
ENC8-7: D4135.1 (K), U422.12 (OUT7)
ENC8-8: D4136.1 (K), U422.20 (OUT15)
ENC8-9: D4137.1 (K), U422.19 (OUT14)
ENC8-10: D4138.1 (K), U422.18 (OUT13)
ENC8-11: D4139.1 (K), U422.17 (OUT12)
ENC8-12: D4140.1 (K), U422.16 (OUT11)
ENC8-13: D4141.1 (K), U422.15 (OUT10)
ENC8-14: D4142.1 (K), U422.14 (OUT9)
ENC8-15: D4143.1 (K), U422.13 (OUT8)
ENC9-0: D4144.1 (K), U423.5 (OUT0)
ENC9-1: D4145.1 (K), U423.6 (OUT1)
ENC9-2: D4146.1 (K), U423.7 (OUT2)
ENC9-3: D4147.1 (K), U423.8 (OUT3)
ENC9-4: D4148.1 (K), U423.9 (OUT4)
ENC9-5: D4149.1 (K), U423.10 (OUT5)
ENC9-6: D4150.1 (K), U423.11 (OUT6)
ENC9-7: D4151.1 (K), U423.12 (OUT7)
ENC9-8: D4152.1 (K), U423.20 (OUT15)
ENC9-9: D4153.1 (K), U423.19 (OUT14)
ENC9-10: D4154.1 (K), U423.18 (OUT13)
ENC9-11: D4155.1 (K), U423.17 (OUT12)
ENC9-12: D4156.1 (K), U423.16 (OUT11)
ENC9-13: D4157.1 (K), U423.15 (OUT10)
ENC9-14: D4158.1 (K), U423.14 (OUT9)
ENC9-15: D4159.1 (K), U423.13 (OUT8)
EOA: SW400.A, U404.2 (A)
EOB: SW400.B, U404.3 (B)
EOS: SW400.S1, U404.4 (SWI)
F0A: MF301.5 (A), U308.6 (OUT1)
F0B: MF301.6 (B), U308.8 (OUT2)
F0P: MF301.2, U304.8 (CH7)
F0T: MF301.4 (T), R305.1
F1A: MF302.5 (A), U309.6 (OUT1)
F1B: MF302.6 (B), U309.8 (OUT2)
F1P: MF302.2, U304.7 (CH6)
F1T: MF302.4 (T), R306.1
F2A: MF303.5 (A), U310.6 (OUT1)
F2B: MF303.6 (B), U310.8 (OUT2)
F2P: MF303.2, U304.6 (CH5)
F2T: MF303.4 (T), R307.1
F3A: MF304.5 (A), U311.6 (OUT1)
F3B: MF304.6 (B), U311.8 (OUT2)
F3P: MF304.2, U304.5 (CH4)
F3T: MF304.4 (T), R308.1
F4A: MF305.5 (A), U312.6 (OUT1)
F4B: MF305.6 (B), U312.8 (OUT2)
F4P: MF305.2, U304.4 (CH3)
F4T: MF305.4 (T), R309.1
FGND: C301.2, C303.2, C304.2, C305.2, C306.2, C307.2, C308.2, C309.2, C310.2, C311.2, C312.2, C313.2, C314.2, C315.2, C316.2, C317.2, C318.2, C319.2, C320.2, C321.2, C322.2, C323.2, C324.2, C325.2, C326.2, C327.2, C328.2, C334.2, C335.2, C336.2, C337.2, C338.1, C339.1, J301.2, J302.1, J309.5, MF301.3, MF301.7 (SHIELD), MF302.3, MF302.7 (SHIELD), MF303.3, MF303.7 (SHIELD), MF304.3, MF304.7 (SHIELD), MF305.3, MF305.7 (SHIELD), R321.1, R322.1, R323.1, R324.1, R325.1, RV301.1, U301.19 (TESTEN), U301.57 (GND), U302.4 (GND), U303.14 (GND), U304.1 (CH0), U304.2 (CH1), U304.3 (CH2), U304.9 (DGND), U304.14 (AGND), U305.2 (A), U306.1 (A0), U306.2 (A1), U306.3 (A2), U306.4 (A3), U306.5 (A4), U306.14 (VSS), U306.24 (A5), U307.10 (VSS), U307.15 (A0), U307.16 (A1), U307.17 (A2), U308.1 (GND), U308.7 (GND), U308.9 (GND), U309.1 (GND), U309.7 (GND), U309.9 (GND), U310.1 (GND), U310.7 (GND), U310.9 (GND), U311.1 (GND), U311.7 (GND), U311.9 (GND), U312.1 (GND), U312.7 (GND), U312.9 (GND)
FKA: J502.1, U503.6 (O1)
FKB: J502.2, U503.4 (O2)
FPEDAL1: J102.7, U101.41 (GPIO29_ADC3)
FSCL: U301.9 (GPIO7), U306.26 (SCL)
FSDA: U301.8 (GPIO6), U306.27 (SDA)
FSPI1DC: DS301.5 (RS), DS302.5 (RS), DS303.5 (RS), DS304.5 (RS), DS305.5 (RS), U301.41 (GPIO29_ADC3)
FSPI1MISO: J309.1, U301.40 (GPIO28_ADC2), U304.12 (Dout), U307.14 (SO)
FSPI1MOSI: DS301.3 (MOSI), DS302.3 (MOSI), DS303.3 (MOSI), DS304.3 (MOSI), DS305.3 (MOSI), J309.2, U301.39 (GPIO27_ADC1), U304.11 (Din), U307.13 (SI)
FSPI1SCK: DS301.4 (SCK), DS302.4 (SCK), DS303.4 (SCK), DS304.4 (SCK), DS305.4 (SCK)
FSPI1SCL: J309.3, U301.38 (GPIO26_ADC0), U304.13 (CLK), U307.12 (SCK)
FSW1: J102.3, U101.34 (GPIO22)
FSW2: J102.4, U101.35 (GPIO23)
F_BOOTSEL: J301.3, R303.2
F_RESET_RP2: J301.4, R304.2, U301.26 (RUN)
F_SWCLK: J301.6, U301.24 (SWCLK)
F_SWDIO: J301.5, U301.25 (SWD)
GND: C101.2, C102.2, C103.2, C104.2, C105.2, C106.2, C107.2, C108.2, C109.2, C110.2, C111.1, C112.1, C113.2, C114.2, C115.2, C116.2, C117.2, C118.2, C119.2, C120.2, C121.2, C122.2, C123.2, C124.2, C125.2, C126.2, C127.1, C128.1, C129.2, C130.2, C201.2, C202.2, C203.2, C501.2, C502.2, C503.2, C504.2, C506.2, C507.2, D101.2 (GND), D102.2 (GND), D103.2 (GND), D104.2 (GND), D105.2 (GND), D106.2 (GND), D107.2 (GND), D108.2 (GND), D109.2 (GND), DS501.8 (GND), DS501.13 (GND), J101.2, J102.2, J103.6, J104.2, J105.4 (GND1), J105.8 (GND2), J106.4 (GND), J201.2, J203.2, J203.6, J204.2, J204.6, J503.3, R110.2, R111.1, U101.19 (TESTEN), U101.57 (GND), U102.4 (GND), U103.2 (A), U104.10 (VSS), U104.15 (A0), U104.16 (A1), U104.17 (A2), U106.1 (USBDM_DN1/PRT_DIS_M1), U106.2 (USBDP_DN1/PRT_DIS_P1), U106.12 (PRTPWR1/BC_EN1), U106.13 (OCS_N1), U106.20 (PRTPWR4/BC_EN4), U106.21 (OCS_N4), U106.37 (VSS), U107.1 (A0), U107.2 (A1), U107.3 (A2), U107.4 (GND), U201.5, U501.19 (GND), U502.8 (GND), U503.3 (GND)
INT-KEYP: R502.2, U501.24 (~INT)
INT_U6: U104.19 (INTB), U104.20 (INTA)
INT_U11: J307.1, U301.7 (GPIO5)
INT_U11-ENC: J308.1, U401.19 (INTB), U401.20 (INTA)
INT_U12: J307.3, U301.5 (GPIO3)
INT_U12-ENC: J308.3, U402.19 (INTB), U402.20 (INTA)
INT_U13: J307.5, U301.3 (GPIO1)
INT_U13-ENC: J308.5, U403.19 (INTB), U403.20 (INTA)
INT_U14: U301.12 (GPIO9), U307.19 (INTB), U307.20 (INTA)
M0A: U306.22 (LED15), U308.3 (IN1)
M0B: U306.21 (LED14), U308.2 (IN2)
M1A: U306.20 (LED13), U309.3 (IN1)
M1B: U306.19 (LED12), U309.2 (IN2)
M2A: U306.18 (LED11), U310.3 (IN1)
M2B: U306.17 (LED10), U310.2 (IN2)
M3A: U306.16 (LED9), U311.3 (IN1)
M3B: U306.15 (LED8), U311.2 (IN2)
M4A: U306.13 (LED7), U312.3 (IN1)
M4B: U306.12 (LED6), U312.2 (IN2)
M-FSW1: J201.5, J205.2 (T)
M-FSW2: J201.6, J206.2 (T)
M-MIDI_RX: J201.3, R201.1, R203.2, U201.4
M-MIDI_TX: J201.4, R205.2
MF-G: J503.5, U502.3 (T1/AG)
MF-T: J503.4, U502.2 (T0)
MIDI_RX: J102.6, U101.37 (GPIO25)
MIDI_TX: J102.5, U101.36 (GPIO24)
MTCH_SENSADJ: RV301.2, U303.11 (SENSADJ), U502.5 (SENSADJ)
unnamed: C112.2, R107.1, X101.1
unnamed: C128.2, R112.1, X201.1
unnamed: C202.1, J202.2
unnamed: C203.1, J202.6
unnamed: C339.2, R301.1, X301.1
unnamed: C426.2, C427.2
unnamed: D201.2 (A), FB202.1, U201.2
unnamed: D201.1 (K), R206.2, U201.1
unnamed: D4096.2 (A), D4097.2 (A), D4098.2 (A), D4099.2 (A), D4100.2 (A), D4101.2 (A), D4102.2 (A), D4103.2 (A), D4104.2 (A), D4105.2 (A), D4106.2 (A), D4107.2 (A), D4108.2 (A), D4109.2 (A), D4110.2 (A), D4111.2 (A), D4166.2 (A)
unnamed: DS301.11 (LEDK), R316.1
unnamed: DS302.11 (LEDK), R317.1
unnamed: DS303.11 (LEDK), R318.1
unnamed: DS304.11 (LEDK), R319.1
unnamed: DS305.11 (LEDK), R320.1
unnamed: FB201.1, R206.1
unnamed: FB201.2, J202.4
unnamed: FB202.2, J202.5
unnamed: FB203.1, R202.1
unnamed: FB203.2, J203.4
unnamed: FB204.1, R203.1
unnamed: FB204.2, J203.5
unnamed: FB205.1, R204.1
unnamed: FB205.2, J204.4
unnamed: FB206.1, R205.1
unnamed: FB206.2, J204.5
unnamed: J311.2, U306.10 (LED4)
unnamed: J311.3, U306.9 (LED3)
unnamed: J311.4, U306.8 (LED2)
unnamed: J311.5, U306.7 (LED1)
unnamed: J311.6, U306.6 (LED0)
unnamed: C111.2, U101.20 (XIN), X101.2
unnamed: R107.2, U101.21 (XOUT)
unnamed: U105.1 (GND), U105.15 (GND), U105.38 (GND), U105.39 (GND)
unnamed: R305.2, U303.2 (T0)
unnamed: R306.2, U303.3 (T1)
unnamed: R307.2, U303.5 (T2/AG)
unnamed: R308.2, U303.6 (T3)
unnamed: R309.2, U303.7 (T4)
unnamed: R321.2, U308.4 (ILIM)
unnamed: R322.2, U309.4 (ILIM)
unnamed: R323.2, U310.4 (ILIM)
unnamed: R324.2, U311.4 (ILIM)
unnamed: R325.2, U312.4 (ILIM)
unnamed: U401.21 (GPA0), U409.7
unnamed: U401.22 (GPA1), U409.6 (D)
unnamed: U401.23 (GPA2), U409.5 (SWO)
unnamed: U401.26 (GPA5), U404.7
unnamed: U401.27 (GPA6), U404.6 (D)
unnamed: U401.28 (GPA7), U404.5 (SWO)
unnamed: U401.1 (GPB0), U405.7
unnamed: U401.2 (GPB1), U405.6 (D)
unnamed: U401.3 (GPB2), U405.5 (SWO)
unnamed: U401.6 (GPB5), U410.7
unnamed: U401.7 (GPB6), U410.6 (D)
unnamed: U401.8 (GPB7), U410.5 (SWO)
unnamed: U402.21 (GPA0), U411.7
unnamed: U402.22 (GPA1), U411.6 (D)
unnamed: U402.23 (GPA2), U411.5 (SWO)
unnamed: U402.26 (GPA5), U406.7
unnamed: U402.27 (GPA6), U406.6 (D)
unnamed: U402.28 (GPA7), U406.5 (SWO)
unnamed: U402.1 (GPB0), U407.7
unnamed: U402.2 (GPB1), U407.6 (D)
unnamed: U402.3 (GPB2), U407.5 (SWO)
unnamed: U402.6 (GPB5), U412.7
unnamed: U402.7 (GPB6), U412.6 (D)
unnamed: U402.8 (GPB7), U412.5 (SWO)
unnamed: U403.1 (GPB0), U408.7
unnamed: U403.2 (GPB1), U408.6 (D)
unnamed: U403.3 (GPB2), U408.5 (SWO)
unnamed: U403.6 (GPB5), U413.7
unnamed: U403.7 (GPB6), U413.6 (D)
unnamed: U403.8 (GPB7), U413.5 (SWO)
unnamed: R401.2, U414.23 (IREF)
unnamed: R402.2, U415.23 (IREF)
unnamed: R403.2, U416.23 (IREF)
unnamed: R404.2, U417.23 (IREF)
unnamed: R405.2, U418.23 (IREF)
unnamed: R406.2, U419.23 (IREF)
unnamed: C418.1, C419.1, U419.24 (VCC)
unnamed: R407.2, U420.23 (IREF)
unnamed: R408.2, U421.23 (IREF)
unnamed: R409.2, U422.23 (IREF)
unnamed: R410.2, U423.23 (IREF)
unnamed: R506.2, U501.2 (ROW6)
unnamed: R507.2, U501.1 (ROW7)
RESET_RP2: J101.4, JP101.1 (A), R101.2, U101.26 (RUN)
RESET_USB: J104.3, U106.26 (RESET_N)
ROW0: SW501.1 (A), SW502.1 (A), SW503.1 (A), SW504.1 (A), SW525.1 (A), U501.8 (ROW0)
ROW1: J504.4, SW505.1 (A), SW506.1 (A), SW507.1 (A), SW508.1 (A), U501.7 (ROW1)
ROW2: J504.3, SW509.1 (A), SW510.1 (A), SW511.1 (A), SW512.1 (A), U501.6 (ROW2)
ROW3: J508.4, SW513.1 (A), SW514.1 (A), SW515.1 (A), SW516.1 (A), U501.5 (ROW3)
ROW4: J508.3, SW517.1 (A), SW518.1 (A), SW519.1 (A), SW520.1 (A), U501.4 (ROW4)
ROW5: SW521.1 (A), SW522.1 (A), SW523.1 (A), SW524.1 (A), U501.3 (ROW5)
RP2_VREF: R106.2, U101.43 (ADC_AVDD), U103.1 (K)
RST-KEYP: R501.2, U501.20 (~RESET)
SCL-KEYP: R503.2, U501.23 (SCL)
SDA-KEYP: R504.2, U501.22 (SDA)
SPI1MISO: U101.15 (GPIO12), U104.14 (SO)
SPI1MISO-ENC: J310.5, U401.14 (SO), U402.14 (SO), U403.14 (SO)
SPI1MOSI: DS501.3 (MOSI), U101.18 (GPIO15), U104.13 (SI)
SPI1MOSI-ENC: J310.4, U401.13 (SI), U402.13 (SI), U403.13 (SI)
SPI1SCK-ENC: J310.3, U401.12 (SCK), U402.12 (SCK), U403.12 (SCK)
SPI1SCL: DS501.4 (SCK), U101.17 (GPIO14), U104.12 (SCK)
SWCLK: J101.6, U101.24 (SWCLK)
SWDIO: J101.5, U101.25 (SWD)
T0: R310.1, U303.13 (O0), U307.25 (GPA4)
T1: R311.1, U303.12 (O1), U307.24 (GPA3)
T2: R312.1, U303.10 (O2/GC), U307.23 (GPA2)
T3: R313.1, U303.9 (O3), U307.22 (GPA1)
T4: R314.1, U303.8 (O4), U307.21 (GPA0)
TLC-BLANK: U414.21 (BLANK), U415.21 (BLANK), U416.21 (BLANK), U417.21 (BLANK), U418.21 (BLANK), U419.21 (BLANK), U420.21 (BLANK), U421.21 (BLANK), U422.21 (BLANK), U423.21 (BLANK)
TLC-LATCH: U414.4 (LATCH), U415.4 (LATCH), U416.4 (LATCH), U417.4 (LATCH), U418.4 (LATCH), U419.4 (LATCH), U420.4 (LATCH), U421.4 (LATCH), U422.4 (LATCH), U423.4 (LATCH)
TLC-SCK: U414.3 (SCLK), U415.3 (SCLK), U416.3 (SCLK), U417.3 (SCLK), U418.3 (SCLK), U419.3 (SCLK), U420.3 (SCLK), U421.3 (SCLK), U422.3 (SCLK), U423.3 (SCLK)
U15_VREF: R315.2, U304.15 (Vref), U305.1 (K)
U17~OE: U301.11 (GPIO8), U306.23 (~OE)
USB_IN_DN: D108.1 (IO), J106.2 (D-), U106.31 (USBDP_UP)
USB_IN_DP: D109.1 (IO), J106.3 (D+), U106.30 (USBDM_UP)
USB_O1_DN: D106.1 (IO), J105.2 (D1-), U106.6 (USBDM_DN3/PRT_DIS_M3)
USB_O1_DP: D107.1 (IO), J105.3 (D1+), U106.7 (USBDP_DN3/PRT_DIS_P3)
USB_O1_VBUS: D102.1 (IO), J105.1 (VBUS1)
USB_O2_DN: D104.1 (IO), J105.6 (D2-), U106.4 (USBDP_DN2/PRT_DIS_P2)
USB_O2_DP: D105.1 (IO), J105.7 (D2+), U106.3 (USBDM_DN2/PRT_DIS_M2)
USB_O2_VBUS: D101.1 (IO), J105.5 (VBUS2)
USB_RP_DN: R103.1, U106.9 (USBDP_DN4/PRT_DIS_P4)
USB_RP_DP: R102.1, U106.8 (USBDM_DN4/PRT_DIS_M4)
USB_SCL: J104.5, U106.24 (SCL/SMBCLK/CFG_SEL0), U107.6 (SCL)
USB_SDA: J104.6, U106.22 (SDA/SMBDATA/NON_REM1), U107.5 (SDA)
VBUS_IN: D103.1 (IO), J106.1 (VBUS), R109.1
VFMOT: C319.1, C320.1, C321.1, C322.1, C323.1, C324.1, C325.1, C326.1, C327.1, C328.1, C506.1, C507.1, U308.5 (VM), U309.5 (VM), U311.5 (VM), U312.5 (VM), U503.5 (MVCC)
exe1-COL4: J505.2, SW526.2 (B), SW532.2 (B)
exe1-COL5: J505.1, SW527.2 (B), SW533.2 (B)
exe1-COL6: J507.4, SW528.2 (B), SW534.2 (B)
exe1-COL7: J507.3, SW529.2 (B), SW535.2 (B)
exe1-COL8: J507.2, SW530.2 (B), SW536.2 (B)
exe1-COL9: J507.1, SW531.2 (B), SW537.2 (B)
exe1-ROW1: J505.3, SW526.1 (A), SW527.1 (A), SW528.1 (A), SW529.1 (A), SW530.1 (A), SW531.1 (A)
exe1-ROW2: J505.4, SW532.1 (A), SW533.1 (A), SW534.1 (A), SW535.1 (A), SW536.1 (A), SW537.1 (A)
exe2-COL4: J509.2, SW538.2 (B), SW544.2 (B)
exe2-COL5: J509.1, SW539.2 (B), SW545.2 (B)
exe2-COL6: J511.4, SW540.2 (B), SW546.2 (B)
exe2-COL7: J511.3, SW541.2 (B), SW547.2 (B)
exe2-COL8: J511.2, SW542.2 (B), SW548.2 (B)
exe2-COL9: J511.1, SW543.2 (B), SW549.2 (B)
exe2-ROW3: J509.3, SW538.1 (A), SW539.1 (A), SW540.1 (A), SW541.1 (A), SW542.1 (A), SW543.1 (A)
exe2-ROW4: J509.4, SW544.1 (A), SW545.1 (A), SW546.1 (A), SW547.1 (A), SW548.1 (A), SW549.1 (A)
~ERST: DS301.6 (~RESET), DS302.6 (~RESET), DS303.6 (~RESET), DS304.6 (~RESET), DS305.6 (~RESET), J312.6, U401.18 (~RESET), U402.18 (~RESET), U403.18 (~RESET)
~FRST: J311.1, U307.18 (~RESET)

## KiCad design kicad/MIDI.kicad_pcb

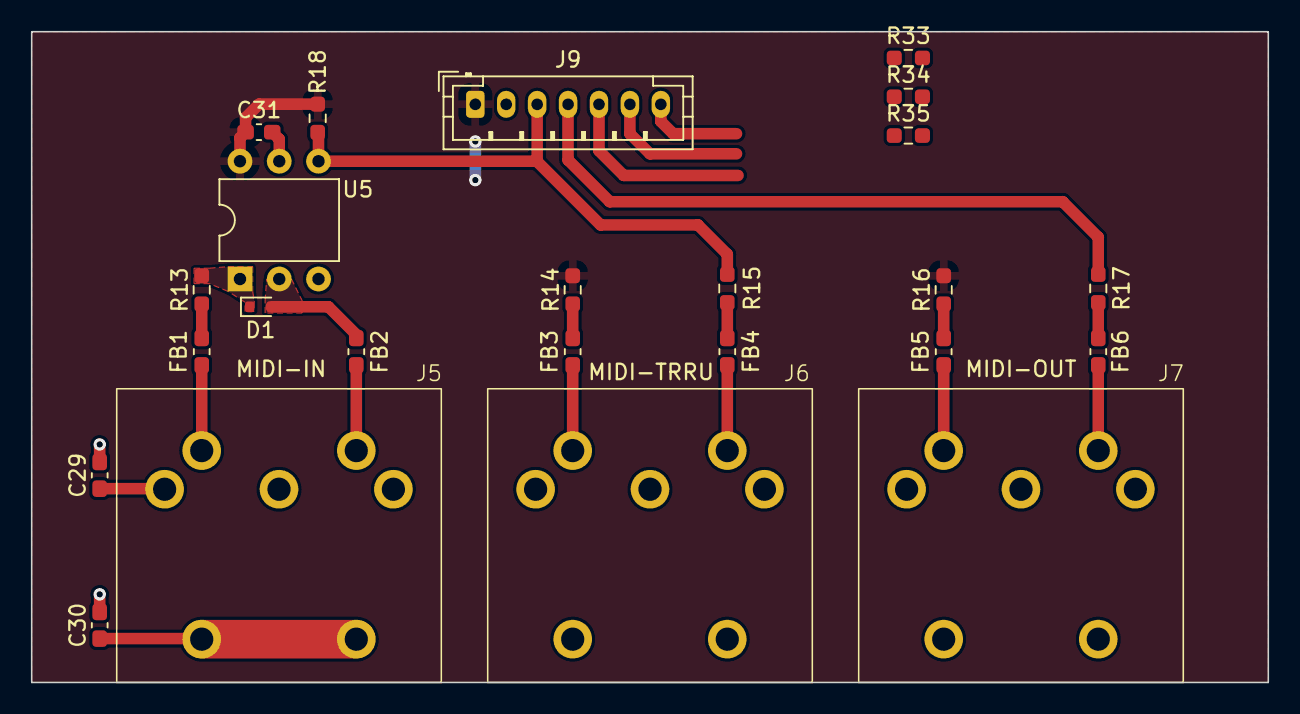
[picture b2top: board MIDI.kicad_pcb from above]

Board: 2 copper layers, 80.0 x 42.1 mm, 24 parts (0 on the bottom side), 22 nets.

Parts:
C29, C30, C31: 100nf; C_0603_1608Metric_Pad1.08x0.95mm_HandSolder
D1: 1N914; D_SOD-523
FB1, FB2, FB3, FB4, FB5, FB6: 1K@100MHz; L_0603_1608Metric_Pad1.05x0.95mm_HandSolder
J5, J6, J7: DIN-5_180degree; DIN5-180
J9: Conn_01x07_Socket; JST_PH_B7B-PH-K_1x07_P2.00mm_Vertical
R13: 220; R_0603_1608Metric_Pad0.98x0.95mm_HandSolder
R14, R16: 33; R_0603_1608Metric_Pad0.98x0.95mm_HandSolder
R15, R17: 10; R_0603_1608Metric_Pad0.98x0.95mm_HandSolder
R18: 470; R_0603_1608Metric_Pad0.98x0.95mm_HandSolder
R33, R34, R35: 10K; R_0603_1608Metric_Pad0.98x0.95mm_HandSolder
U5: H11L1; DIP-6_W7.62mm

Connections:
+3V3: C31.1, J9.1, R14.2, R16.2, R18.2, U5.6
GND: C29.2, C30.2, C31.2, J6.2, J6.6, J7.2, J7.6, J9.2, U5.5
M-FPEDAL1: J9.7, R35.1
M-FSW1: J9.5, R33.1
M-FSW2: J9.6, R34.1
M-MIDI_RX: J9.3, R15.2, R18.1, U5.4
M-MIDI_TX: J9.4, R17.2
unnamed: C29.1, J5.2
unnamed: C30.1, J5.6
unnamed: D1.2 (A), FB2.1, U5.2
unnamed: D1.1 (K), R13.2, U5.1
unnamed: FB1.1, R13.1
unnamed: FB1.2, J5.4
unnamed: FB2.2, J5.5
unnamed: FB3.1, R14.1
unnamed: FB3.2, J6.4
unnamed: FB4.1, R15.1
unnamed: FB4.2, J6.5
unnamed: FB5.1, R16.1
unnamed: FB5.2, J7.4
unnamed: FB6.1, R17.1
unnamed: FB6.2, J7.5
